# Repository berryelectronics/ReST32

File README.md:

# ReST32 - Modular, Open Source 3D Printer Controller
A modular 3D Printer Controller based on the STM32Duino project

This controller is using extra modules for the Heated Bed, Heaters, Extra Extruder Steppers aswell as extra PWM Output for fans and LED's. If you feel to upgrade your printer, just get the module for it. If you manage to damage the MosFET, just swap it out! This brings a low cost base platform, which you can upgrade freely.

- 72Mhz Cortex M3 (STM32F103V)
- 128kb Flash 
- 3 Axis Stepper + 3 Extruder Stepper (1 on the Mainboard)
- 6 Endstop Inputs
- 1 Heated Bed + 1 Thermistor
- 2 Heaters + 2 Thermistors
- High Efficiency 3.3V Buck Converter
- 12V Protected by a proper Car Fuse holder (Heatbed & Electronics)
- (currently) 4 0.6A 12V PWM Channels
- SPI, I2C and Parallel Pinout (Plans for a Full Color Touch GLCD)
- 4 Servo Pinout
- A bulk of Voltage Outputs at one place (4xGND, 4x3V3, 4x5V, 4x12V)

Planned Firmware support:
- Marlin

Modules available:
- Mainboard
- Heatbed Module with AOT240L MosFET and seperate fused 12V Input
- Heater Module with AOT240L MosFET
- Stepper Module to hold 2 more POLOLU Stepper Driver (for usage with dual extrusion or Diamond Hotend)
- Additional Module, with a ULN2803 Darlington Array and 4 0.6A Outputs, for Extruder Fans, LEDs, etc.

Images: 

Sources for Symbols, Footprints and 3D Symbols:

WIP

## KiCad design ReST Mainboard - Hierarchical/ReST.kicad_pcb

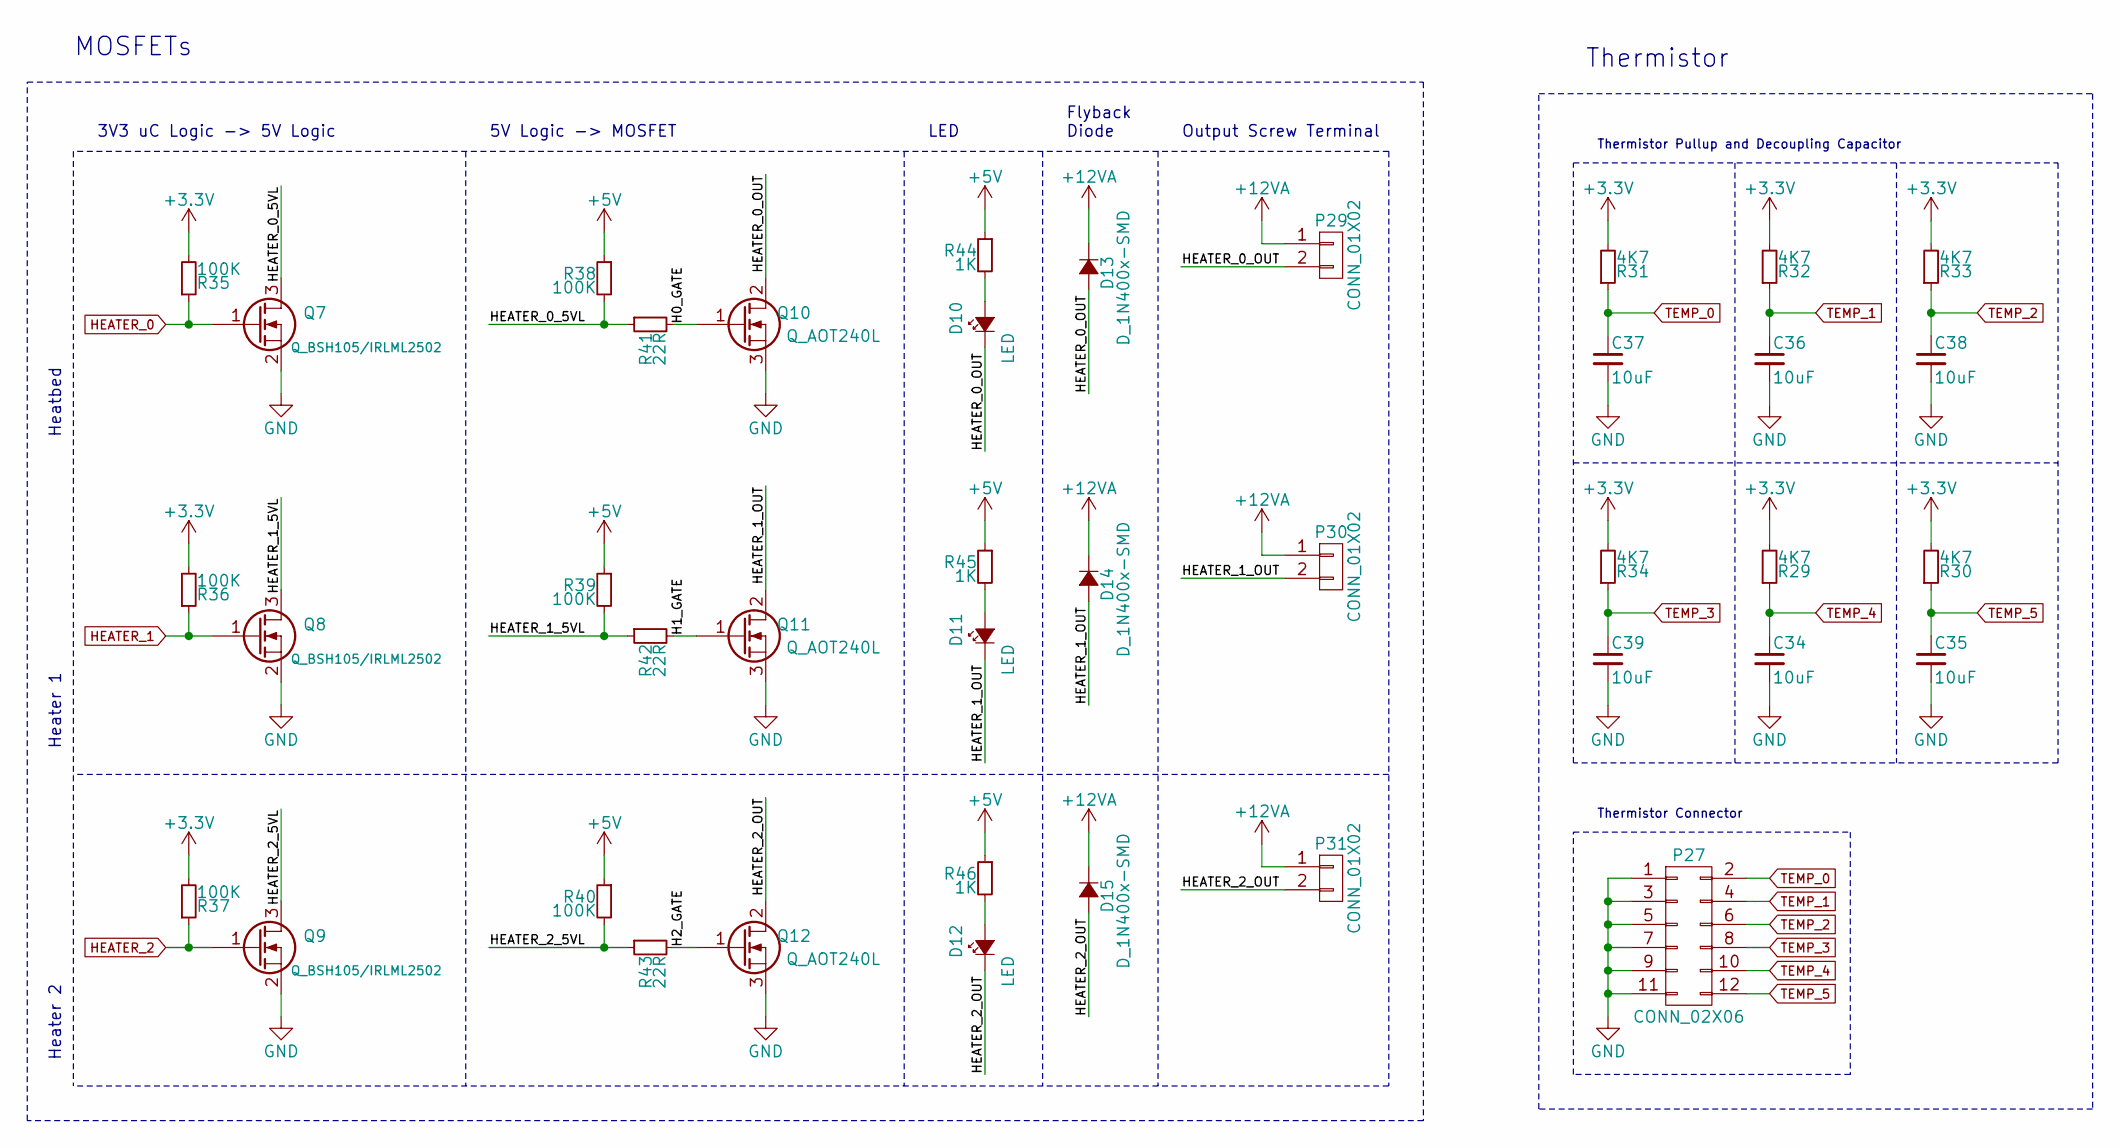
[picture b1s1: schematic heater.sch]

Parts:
C34, C35, C36, C37, C38, C39: 10uF; C_0805_HandSoldering
D10, D11, D12: LED; LED_0805
D13, D14, D15: D_1N400x-SMD; DO-214AC.SMA
P27: CONN_02X06; Pin_Header_Straight_2x06
P29, P30, P31: CONN_01X02; screw-5-2P
Q7, Q8, Q9: Q_BSH105/IRLML2502; SOT-23
Q10, Q11, Q12: Q_AOT240L; TO-220_Neutral123_Vertical_LargePads
R29, R30, R31, R32, R33, R34: 4K7; R_0805_HandSoldering
R35, R36, R37, R38, R39, R40: 100K; R_0603_HandSoldering
R41, R42, R43: 22R; R_0603_HandSoldering
R44, R45, R46: 1K; R_0603_HandSoldering

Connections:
+5V: R38.1, R39.1, R40.1, R44.1, R45.1, R46.1; also elsewhere on the board
+12VA: D13.1 (K), D14.1 (K), D15.1 (K), P29.1, P30.1, P31.1; also elsewhere on the board
/Heater/H0_GATE: Q10.1 (G), R41.2
/Heater/H1_GATE: Q11.1 (G), R42.2
/Heater/H2_GATE: Q12.1 (G), R43.2
/Heater/HEATER_0_5VL: Q7.3 (D), R38.2, R41.1
/Heater/HEATER_0_OUT: D10.1 (K), D13.2 (A), P29.2, Q10.2 (D)
/Heater/HEATER_1_5VL: Q8.3 (D), R39.2, R42.1
/Heater/HEATER_1_OUT: D11.1 (K), D14.2 (A), P30.2, Q11.2 (D)
/Heater/HEATER_2_5VL: Q9.3 (D), R40.2, R43.1
/Heater/HEATER_2_OUT: D12.1 (K), D15.2 (A), P31.2, Q12.2 (D)
GND: C34.2, C35.2, C36.2, C37.2, C38.2, C39.2, P27.1, P27.3, P27.5, P27.7, P27.9, P27.11, Q7.2 (S), Q8.2 (S), Q9.2 (S), Q10.3 (S), Q11.3 (S), Q12.3 (S); also elsewhere on the board
HEATER_0: Q7.1 (G), R35.1; also elsewhere on the board
HEATER_1: Q8.1 (G), R36.1; also elsewhere on the board
HEATER_2: Q9.1 (G), R37.1; also elsewhere on the board
unnamed: D10.2 (A), R44.2
unnamed: D11.2 (A), R45.2
unnamed: D12.2 (A), R46.2
TEMP_0: C37.1, P27.2, R31.1; also elsewhere on the board
TEMP_1: C36.1, P27.4, R32.1; also elsewhere on the board
TEMP_2: C38.1, P27.6, R33.1; also elsewhere on the board
TEMP_3: C39.1, P27.8, R34.1; also elsewhere on the board
TEMP_4: C34.1, P27.10, R29.1; also elsewhere on the board
TEMP_5: C35.1, P27.12, R30.1; also elsewhere on the board

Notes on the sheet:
3V3 uC Logic -> 5V Logic
5V Logic -> MOSFET
LED
Flyback Diode
Output Screw Terminal
Heatbed
Heater 1
Heater 2
MOSFETs
Thermistor Pullup and Decoupling Capacitor
Thermistor Connector
Thermistor

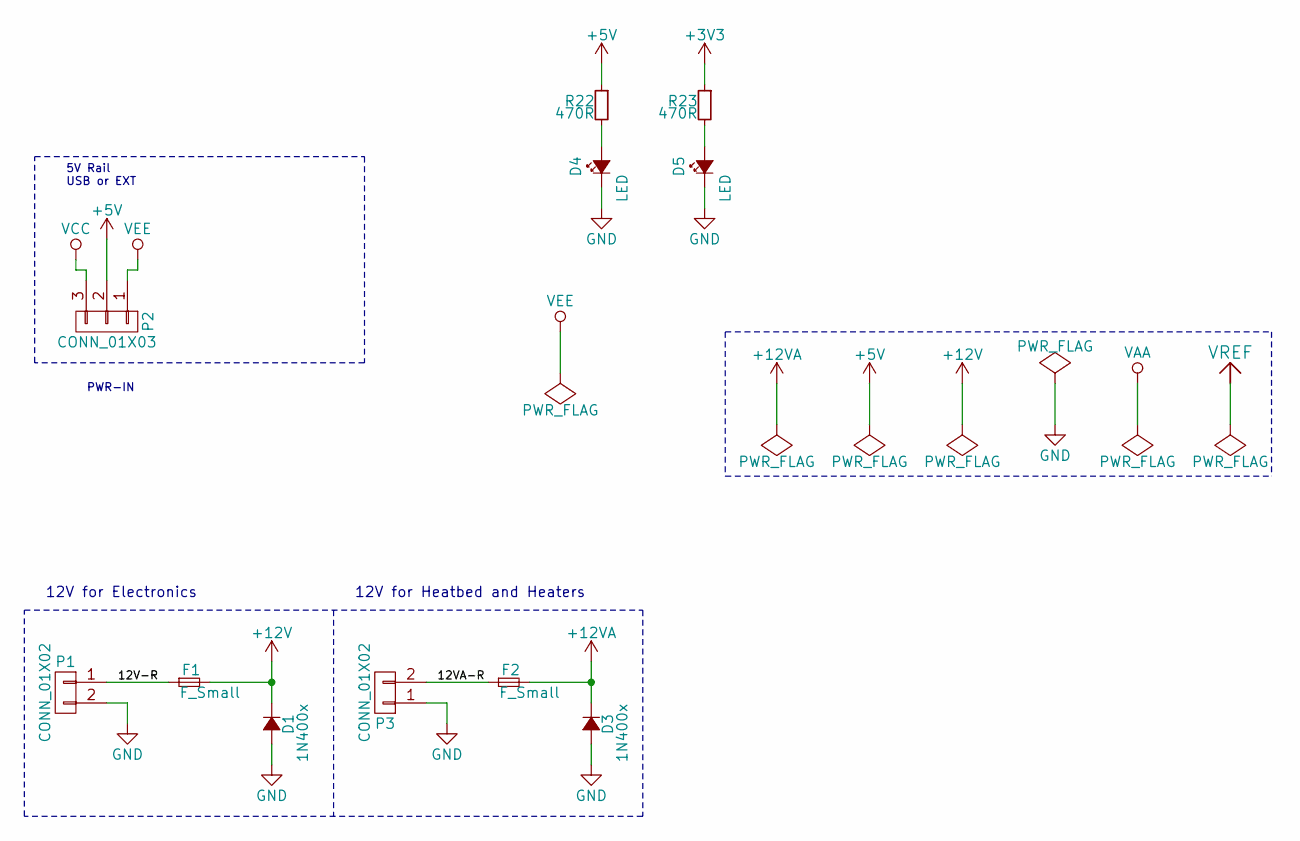
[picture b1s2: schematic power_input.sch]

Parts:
D1, D3: 1N400x; DO-214AC.SMA
D4, D5: LED; LED_0805
F1, F2: F_Small; MINI-FUSE
P1, P3: CONN_01X02; screw-5-2P
P2: CONN_01X03; bb02-hy03a
R22, R23: 470R; R_0603_HandSoldering

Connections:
+5V: P2.2, R22.1; also elsewhere on the board
+12V: D1.1 (K), F1.2; also elsewhere on the board
+12VA: D3.1 (K), F2.2; also elsewhere on the board
/Power Input/12V-R: F1.1, P1.1
/Power Input/12VA-R: F2.1, P3.2
GND: D1.2 (A), D3.2 (A), D4.1 (K), D5.1 (K), P1.2, P3.1; also elsewhere on the board
unnamed: D4.2 (A), R22.2
unnamed: D5.2 (A), R23.2
VCC: P2.3; also elsewhere on the board
VEE: P2.1; also elsewhere on the board

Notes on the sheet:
PWR-IN
5V Rail USB or EXT
12V for Electronics
12V for Heatbed and Heaters

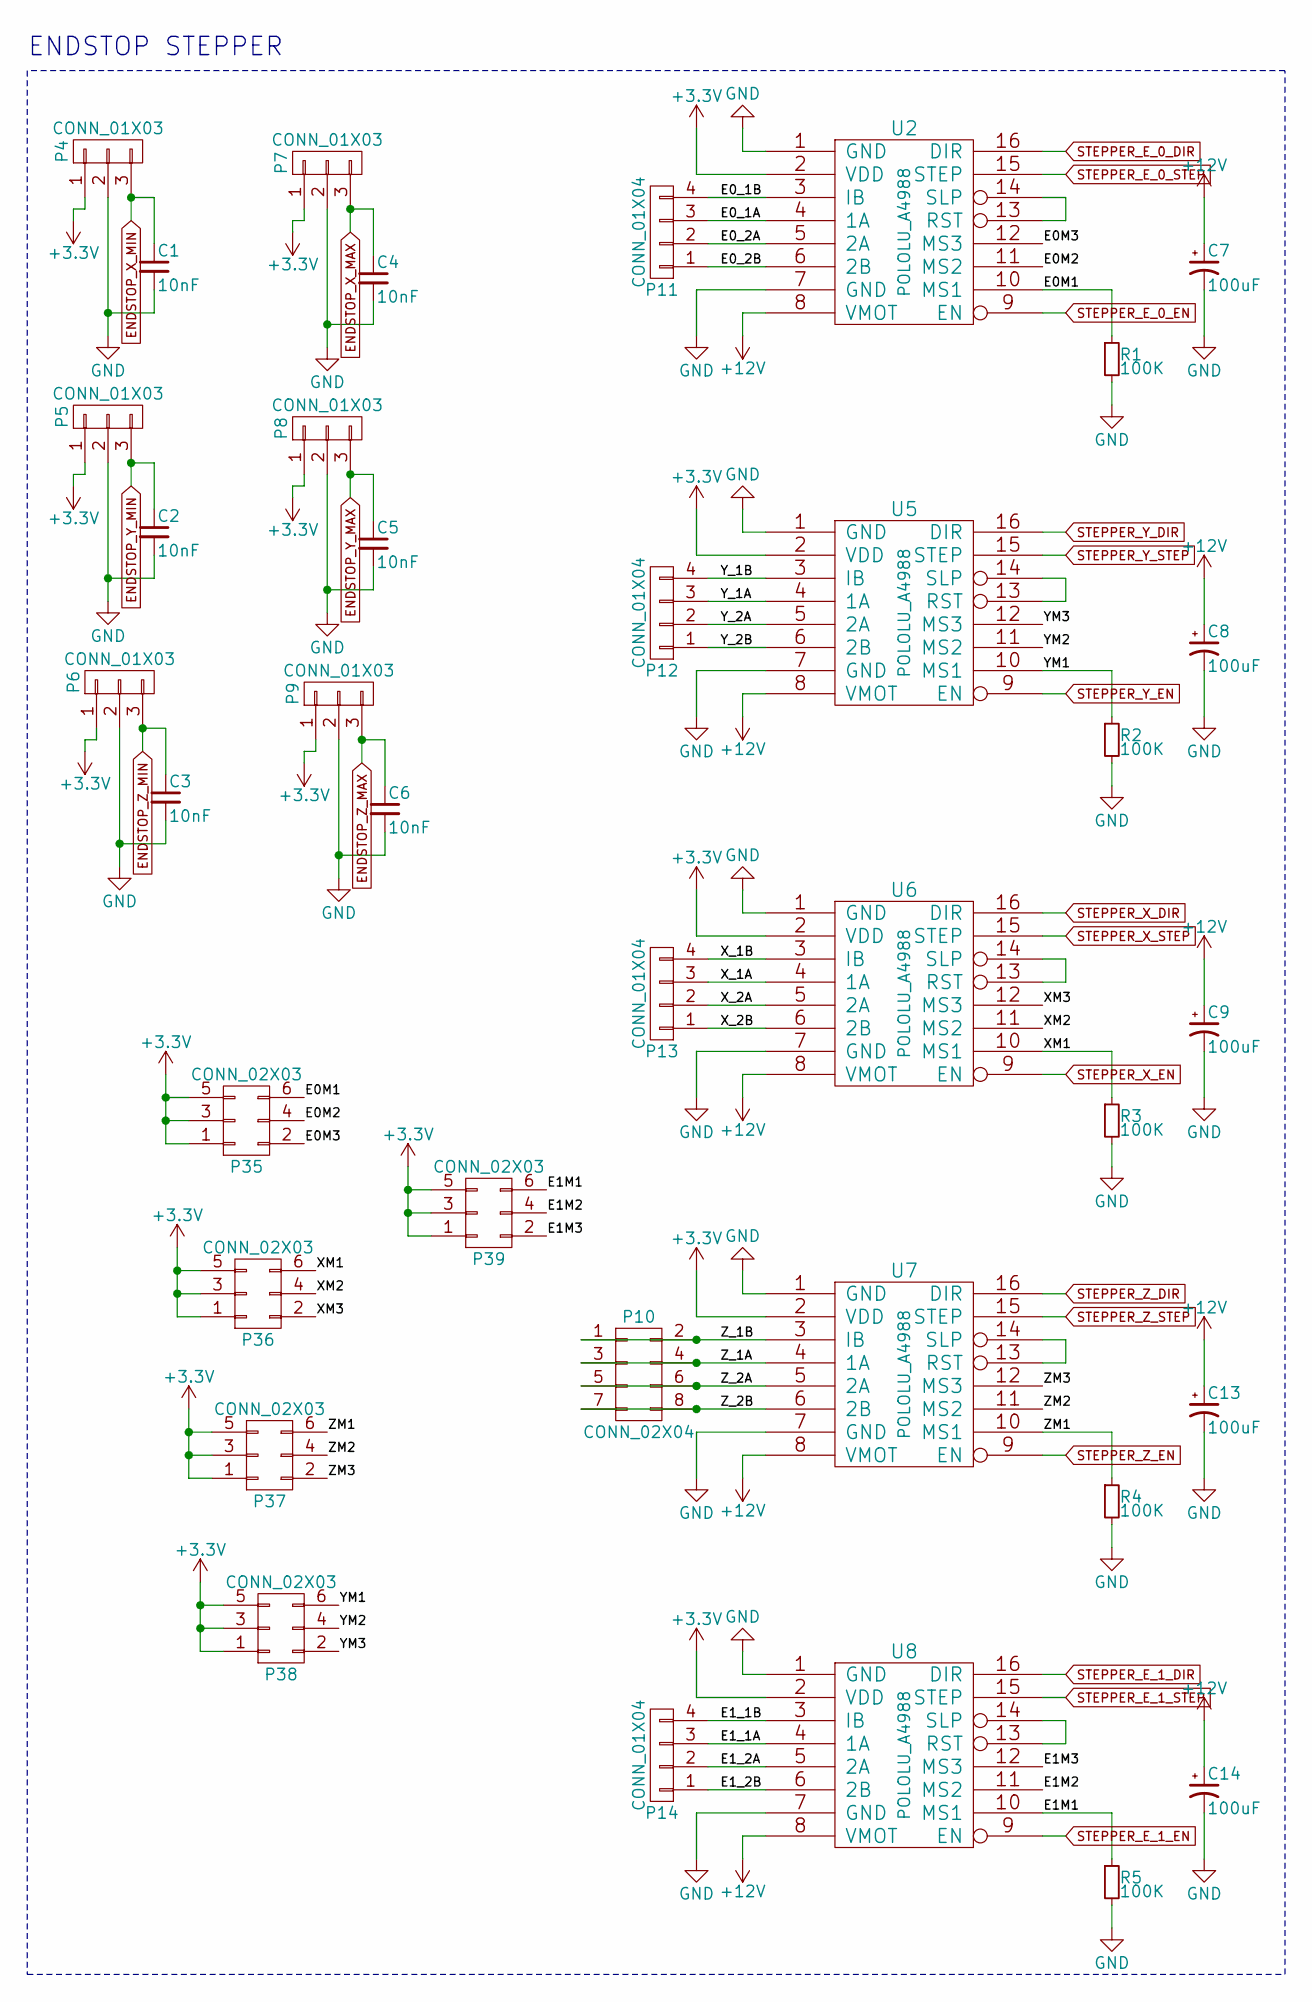
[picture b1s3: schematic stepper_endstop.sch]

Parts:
C1, C2, C3, C4, C5, C6: 10nF; C_0805_HandSoldering
C7, C8, C9, C13, C14: 100uF; CP-PANASONIC-SMT_D8
P4, P5, P6, P7, P8, P9: CONN_01X03; Pin_Header_Straight_1x03
P10: CONN_02X04; Pin_Header_Straight_2x04
P11, P12, P13, P14: CONN_01X04; Pin_Header_Straight_1x04
P35, P36, P37, P38, P39: CONN_02X03; bb02-hp06
R1, R2, R3, R4, R5: 100K; R_0805_HandSoldering
U2, U5, U6, U7, U8: POLOLU_A4988; SWDIP8_.6W

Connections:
+12V: C7.1, C8.1, C9.1, C13.1, C14.1, U2.8 (VMOT), U5.8 (VMOT), U6.8 (VMOT), U7.8 (VMOT), U8.8 (VMOT); also elsewhere on the board
/Stepper and Endstop/E0M1: P35.6, R1.1, U2.10 (MS1)
/Stepper and Endstop/E0M2: P35.4, U2.11 (MS2)
/Stepper and Endstop/E0M3: P35.2, U2.12 (MS3)
/Stepper and Endstop/E0_1A: P11.3, U2.4 (1A)
/Stepper and Endstop/E0_1B: P11.4, U2.3 (IB)
/Stepper and Endstop/E0_2A: P11.2, U2.5 (2A)
/Stepper and Endstop/E0_2B: P11.1, U2.6 (2B)
/Stepper and Endstop/E1M1: P39.6, R5.1, U8.10 (MS1)
/Stepper and Endstop/E1M2: P39.4, U8.11 (MS2)
/Stepper and Endstop/E1M3: P39.2, U8.12 (MS3)
/Stepper and Endstop/E1_1A: P14.3, U8.4 (1A)
/Stepper and Endstop/E1_1B: P14.4, U8.3 (IB)
/Stepper and Endstop/E1_2A: P14.2, U8.5 (2A)
/Stepper and Endstop/E1_2B: P14.1, U8.6 (2B)
/Stepper and Endstop/XM1: P36.6, R3.1, U6.10 (MS1)
/Stepper and Endstop/XM2: P36.4, U6.11 (MS2)
/Stepper and Endstop/XM3: P36.2, U6.12 (MS3)
/Stepper and Endstop/X_1A: P13.3, U6.4 (1A)
/Stepper and Endstop/X_1B: P13.4, U6.3 (IB)
/Stepper and Endstop/X_2A: P13.2, U6.5 (2A)
/Stepper and Endstop/X_2B: P13.1, U6.6 (2B)
/Stepper and Endstop/YM1: P38.6, R2.1, U5.10 (MS1)
/Stepper and Endstop/YM2: P38.4, U5.11 (MS2)
/Stepper and Endstop/YM3: P38.2, U5.12 (MS3)
/Stepper and Endstop/Y_1A: P12.3, U5.4 (1A)
/Stepper and Endstop/Y_1B: P12.4, U5.3 (IB)
/Stepper and Endstop/Y_2A: P12.2, U5.5 (2A)
/Stepper and Endstop/Y_2B: P12.1, U5.6 (2B)
/Stepper and Endstop/ZM1: P37.6, R4.1, U7.10 (MS1)
/Stepper and Endstop/ZM2: P37.4, U7.11 (MS2)
/Stepper and Endstop/ZM3: P37.2, U7.12 (MS3)
/Stepper and Endstop/Z_1A: P10.3, P10.4, U7.4 (1A)
/Stepper and Endstop/Z_1B: P10.1, P10.2, U7.3 (IB)
/Stepper and Endstop/Z_2A: P10.5, P10.6, U7.5 (2A)
/Stepper and Endstop/Z_2B: P10.7, P10.8, U7.6 (2B)
ENDSTOP_X_MAX: C4.1, P7.3; also elsewhere on the board
ENDSTOP_X_MIN: C1.1, P4.3; also elsewhere on the board
ENDSTOP_Y_MAX: C5.1, P8.3; also elsewhere on the board
ENDSTOP_Y_MIN: C2.1, P5.3; also elsewhere on the board
ENDSTOP_Z_MAX: C6.1, P9.3; also elsewhere on the board
ENDSTOP_Z_MIN: C3.1, P6.3; also elsewhere on the board
GND: C1.2, C2.2, C3.2, C4.2, C5.2, C6.2, C7.2, C8.2, C9.2, C13.2, C14.2, P4.2, P5.2, P6.2, P7.2, P8.2, P9.2, R1.2, R2.2, R3.2, R4.2, R5.2, U2.1 (GND), U2.7 (GND), U5.1 (GND), U5.7 (GND), U6.1 (GND), U6.7 (GND), U7.1 (GND), U7.7 (GND), U8.1 (GND), U8.7 (GND); also elsewhere on the board
unnamed: U2.13 (RST), U2.14 (SLP)
unnamed: U5.13 (RST), U5.14 (SLP)
unnamed: U6.13 (RST), U6.14 (SLP)
unnamed: U7.13 (RST), U7.14 (SLP)
unnamed: U8.13 (RST), U8.14 (SLP)
STEPPER_E_0_DIR: U2.16 (DIR); also elsewhere on the board
STEPPER_E_0_EN: U2.9 (EN); also elsewhere on the board
STEPPER_E_0_STEP: U2.15 (STEP); also elsewhere on the board
STEPPER_E_1_DIR: U8.16 (DIR); also elsewhere on the board
STEPPER_E_1_EN: U8.9 (EN); also elsewhere on the board
STEPPER_E_1_STEP: U8.15 (STEP); also elsewhere on the board
STEPPER_X_DIR: U6.16 (DIR); also elsewhere on the board
STEPPER_X_EN: U6.9 (EN); also elsewhere on the board
STEPPER_X_STEP: U6.15 (STEP); also elsewhere on the board
STEPPER_Y_DIR: U5.16 (DIR); also elsewhere on the board
STEPPER_Y_EN: U5.9 (EN); also elsewhere on the board
STEPPER_Y_STEP: U5.15 (STEP); also elsewhere on the board
STEPPER_Z_DIR: U7.16 (DIR); also elsewhere on the board
STEPPER_Z_EN: U7.9 (EN); also elsewhere on the board
STEPPER_Z_STEP: U7.15 (STEP); also elsewhere on the board

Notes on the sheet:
ENDSTOP STEPPER

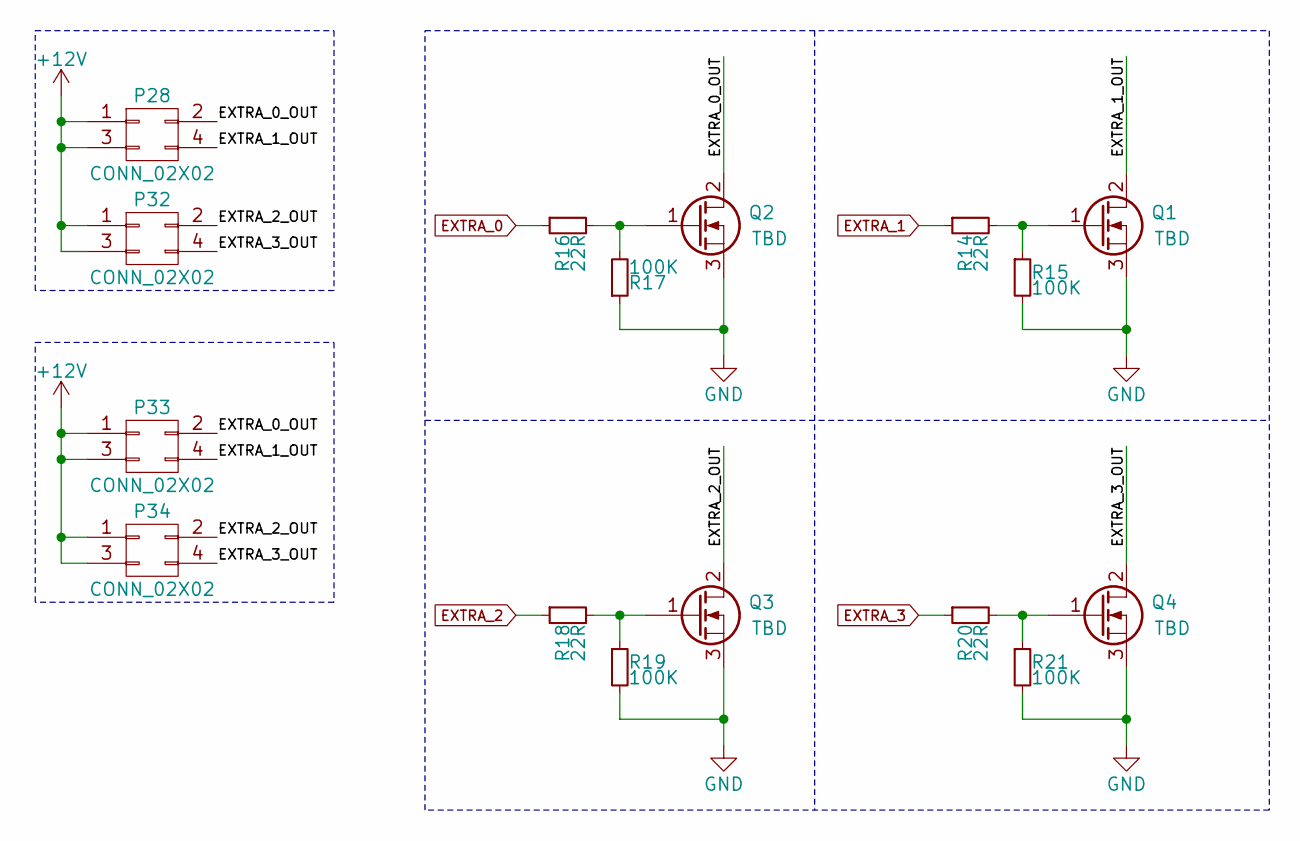
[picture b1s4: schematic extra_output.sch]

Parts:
P28, P32: CONN_02X02; pt_1,5-4-3,5-h
P33, P34: CONN_02X02; Pin_Header_Straight_1x04
Q1, Q2, Q3, Q4: TBD; SOT-23
R14, R16, R18, R20: 22R; R_0603_HandSoldering
R15, R17, R19, R21: 100K; R_0603_HandSoldering

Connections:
+12V: P28.1, P28.3, P32.1, P32.3, P33.1, P33.3, P34.1, P34.3; also elsewhere on the board
/Extra Power Output/EXTRA_0_OUT: P28.2, P33.2, Q2.2 (D)
/Extra Power Output/EXTRA_1_OUT: P28.4, P33.4, Q1.2 (D)
/Extra Power Output/EXTRA_2_OUT: P32.2, P34.2, Q3.2 (D)
/Extra Power Output/EXTRA_3_OUT: P32.4, P34.4, Q4.2 (D)
EXTRA_0: R16.1; also elsewhere on the board
EXTRA_1: R14.1; also elsewhere on the board
EXTRA_2: R18.1; also elsewhere on the board
EXTRA_3: R20.1; also elsewhere on the board
GND: Q1.3 (S), Q2.3 (S), Q3.3 (S), Q4.3 (S), R15.2, R17.1, R19.2, R21.2; also elsewhere on the board
unnamed: Q1.1 (G), R14.2, R15.1
unnamed: Q2.1 (G), R16.2, R17.2
unnamed: Q3.1 (G), R18.2, R19.1
unnamed: Q4.1 (G), R20.2, R21.1

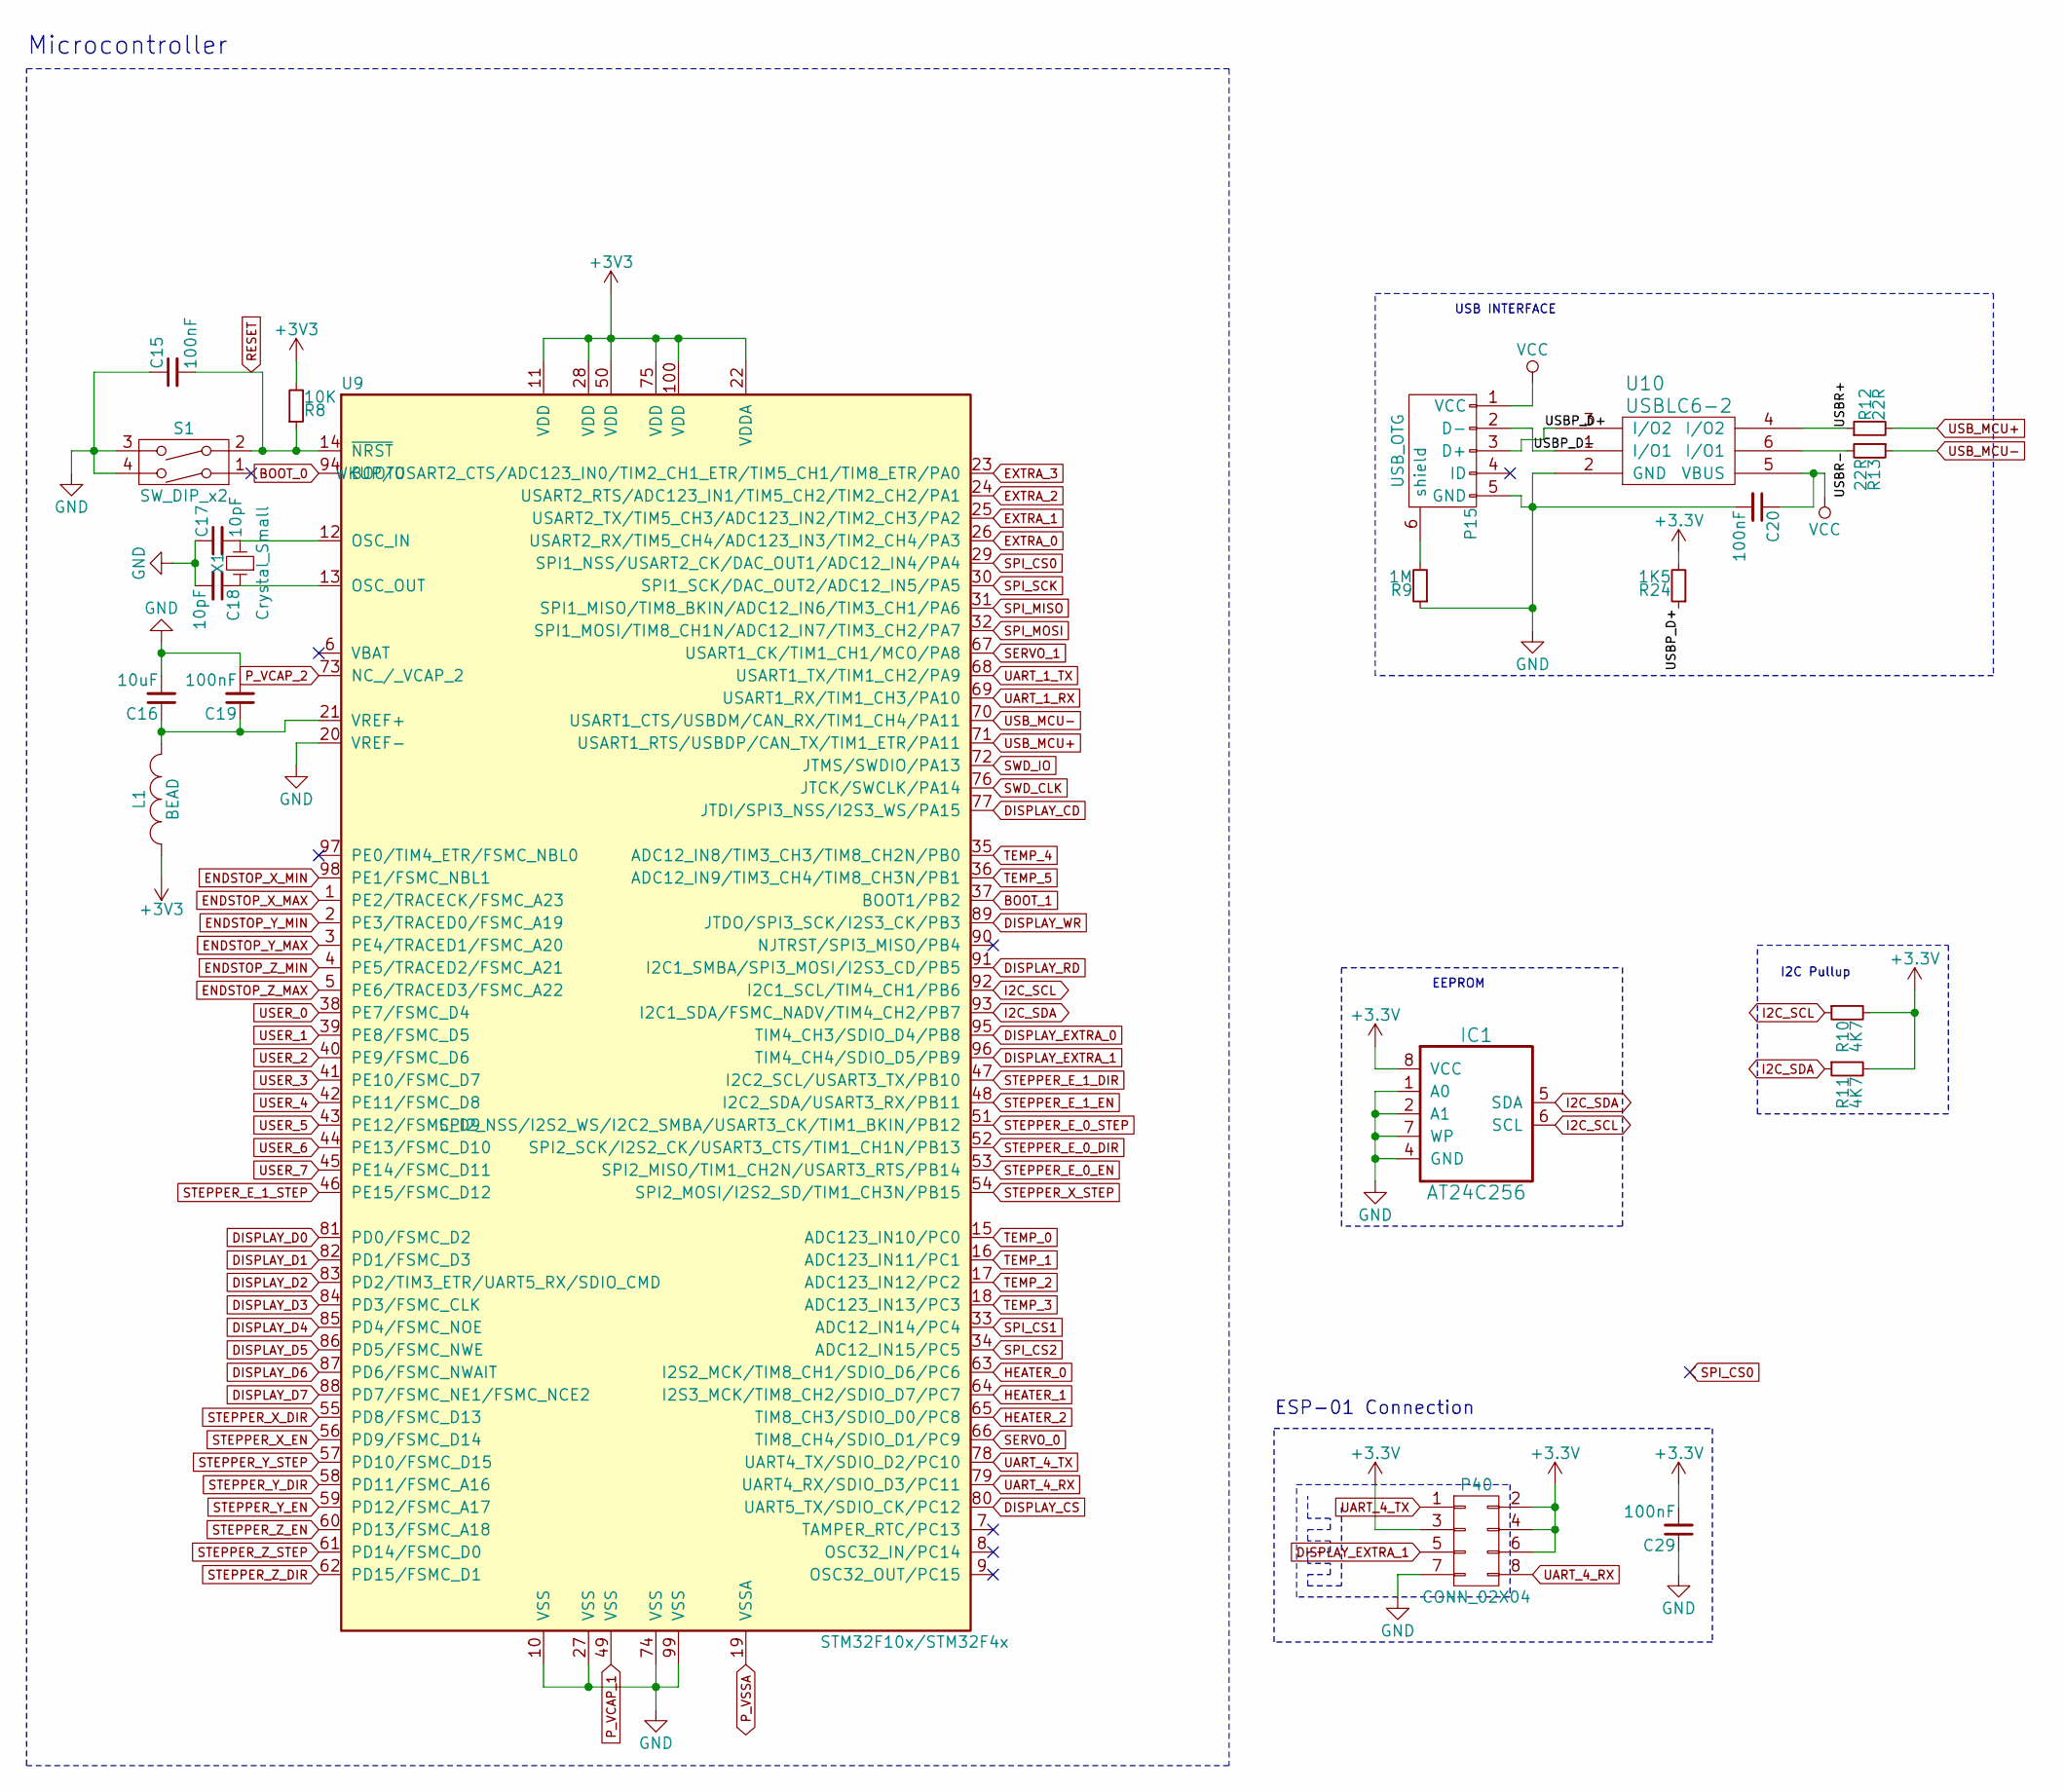
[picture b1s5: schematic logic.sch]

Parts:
C15: 100nF; R_0805_HandSoldering
C16: 10uF; C_0805_HandSoldering
C17, C18: 10pF; R_0805_HandSoldering
C19, C20, C29: 100nF; C_0805_HandSoldering
IC1: AT24C256; SOIC-8_3.9x4.9mm_Pitch1.27mm
L1: BEAD; C_0805_HandSoldering
P15: USB_OTG; USB_Mini-B
P40: CONN_02X04; Pin_Header_Straight_2x04
R8: 10K; R_0805_HandSoldering
R9: 1M; R_0805_HandSoldering
R10, R11: 4K7; R_0805_HandSoldering
R12, R13: 22R; R_0805_HandSoldering
R24: 1K5; R_0805_HandSoldering
S1: SW_DIP_x2; SMD-BUTTON-6MM
U9: STM32F10x/STM32F4x; LQFP100-14x14
U10: USBLC6-2; SOT32-6L
X1: Crystal_Small; 2P-5032

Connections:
/Logic/USBP_D+: P15.3 (D+), R24.1, U10.3 (I/O2)
/Logic/USBP_D-: P15.2 (D-), U10.1 (I/O1)
/Logic/USBR+: R12.1, U10.4 (I/O2)
/Logic/USBR-: R13.2, U10.6 (I/O1)
BOOT_0: U9.94 (BOOT0); also elsewhere on the board
BOOT_1: U9.37 (BOOT1/PB2); also elsewhere on the board
DISPLAY_CD: U9.77 (JTDI/SPI3_NSS/I2S3_WS/PA15); also elsewhere on the board
DISPLAY_CS: U9.80 (UART5_TX/SDIO_CK/PC12); also elsewhere on the board
DISPLAY_D0: U9.81 (PD0/FSMC_D2); also elsewhere on the board
DISPLAY_D1: U9.82 (PD1/FSMC_D3); also elsewhere on the board
DISPLAY_D2: U9.83 (PD2/TIM3_ETR/UART5_RX/SDIO_CMD); also elsewhere on the board
DISPLAY_D3: U9.84 (PD3/FSMC_CLK); also elsewhere on the board
DISPLAY_D4: U9.85 (PD4/FSMC_NOE); also elsewhere on the board
DISPLAY_D5: U9.86 (PD5/FSMC_NWE); also elsewhere on the board
DISPLAY_D6: U9.87 (PD6/FSMC_NWAIT); also elsewhere on the board
DISPLAY_D7: U9.88 (PD7/FSMC_NE1/FSMC_NCE2); also elsewhere on the board
DISPLAY_EXTRA_0: U9.95 (TIM4_CH3/SDIO_D4/PB8); also elsewhere on the board
DISPLAY_EXTRA_1: P40.5, U9.96 (TIM4_CH4/SDIO_D5/PB9)
DISPLAY_RD: U9.91 (I2C1_SMBA/SPI3_MOSI/I2S3_CD/PB5); also elsewhere on the board
DISPLAY_WR: U9.89 (JTDO/SPI3_SCK/I2S3_CK/PB3); also elsewhere on the board
ENDSTOP_X_MAX: U9.1 (PE2/TRACECK/FSMC_A23); also elsewhere on the board
ENDSTOP_X_MIN: U9.98 (PE1/FSMC_NBL1); also elsewhere on the board
ENDSTOP_Y_MAX: U9.3 (PE4/TRACED1/FSMC_A20); also elsewhere on the board
ENDSTOP_Y_MIN: U9.2 (PE3/TRACED0/FSMC_A19); also elsewhere on the board
ENDSTOP_Z_MAX: U9.5 (PE6/TRACED3/FSMC_A22); also elsewhere on the board
ENDSTOP_Z_MIN: U9.4 (PE5/TRACED2/FSMC_A21); also elsewhere on the board
EXTRA_0: U9.26 (USART2_RX/TIM5_CH4/ADC123_IN3/TIM2_CH4/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); also elsewhere on the board
EXTRA_1: U9.25 (USART2_TX/TIM5_CH3/ADC123_IN2/TIM2_CH3/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); also elsewhere on the board
EXTRA_2: U9.24 (USART2_RTS/ADC123_IN1/TIM5_CH2/TIM2_CH2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); also elsewhere on the board
EXTRA_3: U9.23 (WKUP/USART2_CTS/ADC123_IN0/TIM2_CH1_ETR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); also elsewhere on the board
GND: C15.1, C16.2, C17.1, C18.2, C19.2, C20.2, C29.1, IC1.1 (A0), IC1.2 (A1), IC1.4 (GND), IC1.7 (WP), P15.5 (GND), P40.7, R9.1, S1.3, S1.4, U9.10 (VSS), U9.20 (VREF-), U9.27 (VSS), U9.74 (VSS), U9.99 (VSS), U10.2 (GND); also elsewhere on the board
HEATER_0: U9.63 (I2S2_MCK/TIM8_CH1/SDIO_D6/PC6); also elsewhere on the board
HEATER_1: U9.64 (I2S3_MCK/TIM8_CH2/SDIO_D7/PC7); also elsewhere on the board
HEATER_2: U9.65 (TIM8_CH3/SDIO_D0/PC8); also elsewhere on the board
I2C_SCL: IC1.6 (SCL), R10.1, U9.92 (I2C1_SCL/TIM4_CH1/PB6); also elsewhere on the board
I2C_SDA: IC1.5 (SDA), R11.1, U9.93 (I2C1_SDA/FSMC_NADV/TIM4_CH2/PB7); also elsewhere on the board
unnamed: C16.1, C19.1, L1.2, U9.21 (VREF+)
unnamed: C17.2, U9.12 (OSC_IN), X1.2
unnamed: C18.1, U9.13 (OSC_OUT), X1.1
unnamed: P15.6 (shield), R9.2
P_VCAP_1: U9.49 (VSS); also elsewhere on the board
P_VCAP_2: U9.73 (NC_/_VCAP_2); also elsewhere on the board
P_VSSA: U9.19 (VSSA); also elsewhere on the board
RESET: C15.2, R8.1, S1.2, U9.14 (~NRST); also elsewhere on the board
SERVO_0: U9.66 (TIM8_CH4/SDIO_D1/PC9); also elsewhere on the board
SERVO_1: U9.67 (USART1_CK/TIM1_CH1/MCO/PA8); also elsewhere on the board
SPI_CS1: U9.33 (ADC12_IN14/PC4); also elsewhere on the board
SPI_CS2: U9.34 (ADC12_IN15/PC5); also elsewhere on the board
SPI_MISO: U9.31 (SPI1_MISO/TIM8_BKIN/ADC12_IN6/TIM3_CH1/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); also elsewhere on the board
SPI_MOSI: U9.32 (SPI1_MOSI/TIM8_CH1N/ADC12_IN7/TIM3_CH2/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); also elsewhere on the board
SPI_SCK: U9.30 (SPI1_SCK/DAC_OUT2/ADC12_IN5/PA5); also elsewhere on the board
STEPPER_E_0_DIR: U9.52 (SPI2_SCK/I2S2_CK/USART3_CTS/TIM1_CH1N/P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); also elsewhere on the board
STEPPER_E_0_EN: U9.53 (SPI2_MISO/TIM1_CH2N/USART3_RTS/PB14); also elsewhere on the board
STEPPER_E_0_STEP: U9.51 (SPI2_NSS/I2S2_WS/I2C2_SMBA/USART3_CK/TI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); also elsewhere on the board
STEPPER_E_1_DIR: U9.47 (I2C2_SCL/USART3_TX/PB10); also elsewhere on the board
STEPPER_E_1_EN: U9.48 (I2C2_SDA/USART3_RX/PB11); also elsewhere on the board
STEPPER_E_1_STEP: U9.46 (PE15/FSMC_D12); also elsewhere on the board
STEPPER_X_DIR: U9.55 (PD8/FSMC_D13); also elsewhere on the board
STEPPER_X_EN: U9.56 (PD9/FSMC_D14); also elsewhere on the board
STEPPER_X_STEP: U9.54 (SPI2_MOSI/I2S2_SD/TIM1_CH3N/PB15); also elsewhere on the board
STEPPER_Y_DIR: U9.58 (PD11/FSMC_A16); also elsewhere on the board
STEPPER_Y_EN: U9.59 (PD12/FSMC_A17); also elsewhere on the board
STEPPER_Y_STEP: U9.57 (PD10/FSMC_D15); also elsewhere on the board
STEPPER_Z_DIR: U9.62 (PD15/FSMC_D1); also elsewhere on the board
STEPPER_Z_EN: U9.60 (PD13/FSMC_A18); also elsewhere on the board
STEPPER_Z_STEP: U9.61 (PD14/FSMC_D0); also elsewhere on the board
SWD_CLK: U9.76 (JTCK/SWCLK/PA14); also elsewhere on the board
SWD_IO: U9.72 (JTMS/SWDIO/PA13); also elsewhere on the board
TEMP_0: U9.15 (ADC123_IN10/PC0); also elsewhere on the board
TEMP_1: U9.16 (ADC123_IN11/PC1); also elsewhere on the board
TEMP_2: U9.17 (ADC123_IN12/PC2); also elsewhere on the board
TEMP_3: U9.18 (ADC123_IN13/PC3); also elsewhere on the board
TEMP_4: U9.35 (ADC12_IN8/TIM3_CH3/TIM8_CH2N/PB0); also elsewhere on the board
TEMP_5: U9.36 (ADC12_IN9/TIM3_CH4/TIM8_CH3N/PB1); also elsewhere on the board
UART_1_RX: U9.69 (USART1_RX/TIM1_CH3/PA10); also elsewhere on the board
UART_1_TX: U9.68 (USART1_TX/TIM1_CH2/PA9); also elsewhere on the board
UART_4_RX: P40.8, U9.79 (UART4_RX/SDIO_D3/PC11)
UART_4_TX: P40.1, U9.78 (UART4_TX/SDIO_D2/PC10)
USB_MCU+: R12.2, U9.71 (USART1_RTS/USBDP/CAN_TX/TIM1_ETR/PA11)
USB_MCU-: R13.1, U9.70 (USART1_CTS/USBDM/CAN_RX/TIM1_CH4/PA11)
USER_0: U9.38 (PE7/FSMC_D4); also elsewhere on the board
USER_1: U9.39 (PE8/FSMC_D5); also elsewhere on the board
USER_2: U9.40 (PE9/FSMC_D6); also elsewhere on the board
USER_3: U9.41 (PE10/FSMC_D7); also elsewhere on the board
USER_4: U9.42 (PE11/FSMC_D8); also elsewhere on the board
USER_5: U9.43 (PE12/FSMC_D9); also elsewhere on the board
USER_6: U9.44 (PE13/FSMC_D10); also elsewhere on the board
USER_7: U9.45 (PE14/FSMC_D11); also elsewhere on the board
VCC: C20.1, P15.1 (VCC), U10.5 (VBUS); also elsewhere on the board

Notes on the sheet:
EEPROM
I2C Pullup
Microcontroller
USB INTERFACE
ESP-01 Connection
